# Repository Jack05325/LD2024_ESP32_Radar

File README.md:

# LD2420 Radar ESP32

## Descrizione del Progetto

Questo progetto contiene i file di progettazione PCB per un modulo radar basato sul sensore LD2420 integrato con un microcontrollore ESP32. Il sensore LD2420 è un radar a onde millimetriche a 24GHz per il rilevamento di presenza umana, ideale per applicazioni di domotica e automazione.

### Caratteristiche Principali

- **Sensore Radar**: LD2420 a 24GHz per rilevamento preciso di presenza e movimento
- **Microcontrollore**: ESP32 con connettività WiFi e Bluetooth integrata
- **Formato PCB**: Design compatto e ottimizzato per facile integrazione
- **Output**: Dati di rilevamento elaborabili via WiFi/Bluetooth

### Contenuto del Repository

- **File KiCad**: Schema elettrico (.kicad_sch) e layout PCB (.kicad_pcb)
- **BOM**: Bill of Materials nella cartella `/bom`
- **Gerber**: File pronti per la produzione nella cartella `/gerber_to_order`
- **PDF**: Schema elettrico esportato in formato PDF
- **Backup**: Versioni precedenti del progetto in `/LD2420_Radar_ESP32-backups`

### Software Richiesto

- KiCad 7.0 o superiore per aprire e modificare i file di progetto

### Note di Produzione

I file Gerber pronti per l'ordine sono disponibili nella cartella `gerber_to_order`. Consultare il PDF dello schema per i dettagli sul circuito.

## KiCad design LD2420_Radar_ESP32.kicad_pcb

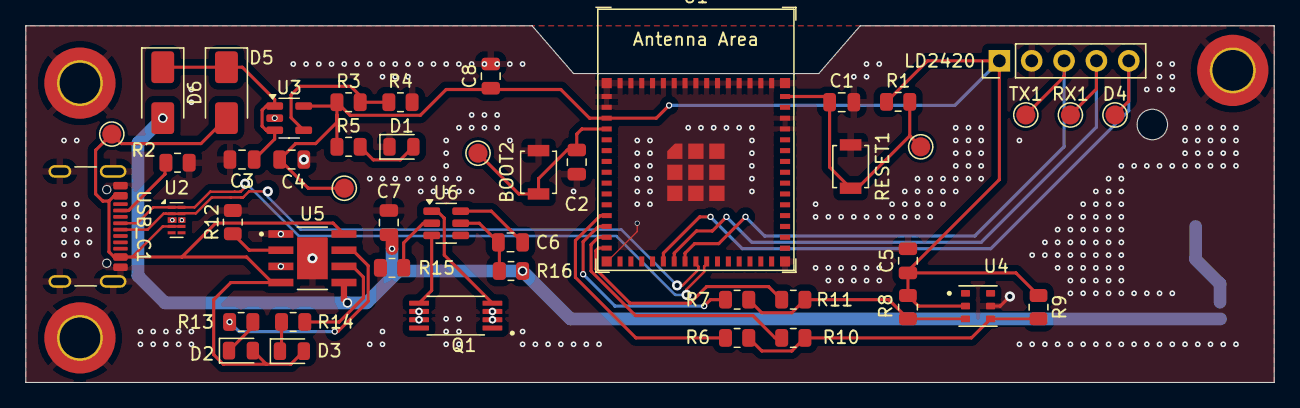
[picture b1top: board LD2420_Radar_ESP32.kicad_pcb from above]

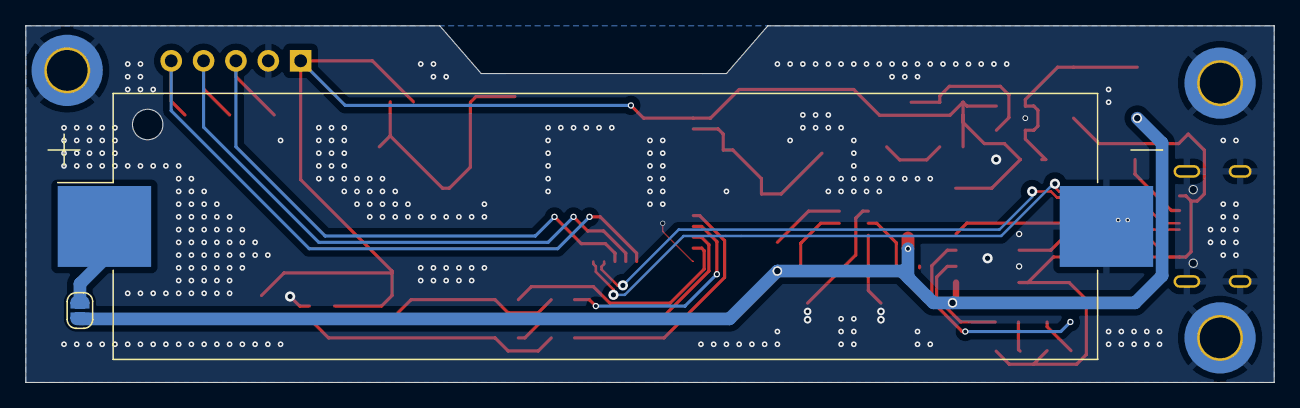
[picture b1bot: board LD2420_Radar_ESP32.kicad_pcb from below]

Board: 2 copper layers, 98.0 x 28.0 mm, 52 parts (2 on the bottom side), 32 nets.

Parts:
3.3V1: TestPoint; TestPoint_Pad_D1.5mm
BOOT1: TestPoint; TestPoint_Pad_D1.5mm
BOOT2: SW_Push; SW_SPST_B3U-1000P
BT1: Battery_Cell; BatteryHolder_Keystone_1042_1x18650
C1, C2, C5: 0.1uF; C_0805_2012Metric
C3, C4, C7, C8: 10uF; C_0805_2012Metric
C6: 100nF; C_0805_2012Metric
D1, D2, D3: LED; LED_0805_2012Metric
D4: TestPoint; TestPoint_Pad_D1.5mm
D5, D6: D; D_SMA
H1, H2, H3: MountingHole_Pad; MountingHole_3.2mm_M3_DIN965_Pad_TopBottom
JP1: Jumper_2_Open; SolderJumper-2_P1.3mm_Open_RoundedPad1.0x1.5mm
LD2420: Conn_01x05_Pin; PinHeader_1x05_P2.54mm_Vertical
Q1: FS8205A; SOP65P640X120-8N
R1: 10K; R_0805_2012Metric
R2: 5.1K; R_0805_2012Metric
R3: 1M; R_0805_2012Metric
R4: 200K; R_0805_2012Metric
R5: 5.1k; R_0805_2012Metric
R6, R7, R10, R11: 0; R_0805_2012Metric
R8, R9: 4.7k; R_0805_2012Metric
R12: 1.2K; R_0805_2012Metric
R13, R14: 1K; R_0805_2012Metric
R15: 1k; R_0805_2012Metric
R16: 100; R_0805_2012Metric
RESET1: SW_Push; SW_SPST_B3U-1000P
RESET2: TestPoint; TestPoint_Pad_D1.5mm
RX1: TestPoint; TestPoint_Pad_D1.5mm
TX1: TestPoint; TestPoint_Pad_D1.5mm
U1: ESP32-S3-MINI-1
U2: D3V3XA4B10LP; Diodes_UDFN-10_1.0x2.5mm_P0.5mm
U3: TLV75801PDBV; SOT-23-5
U4: AHT20; PSON100P300X300X110-6N
U5: TP4056-42-ESOP8; SOIC127P600X175-9N
U6: DW01A; SOT-23-6
USB_C1: USB_C_Plug_USB2.0; USB_C_Receptacle_GCT_USB4105-xx-A_16P_TopMnt_Horizontal
VBUS1: TestPoint; TestPoint_Pad_D1.5mm

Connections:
+3.3V: 3.3V1.1, C4.1, C5.1, C8.1, LD2420.1, R1.1, R3.1, R5.1, R8.1, R9.1, U1.3 (3V3), U3.5 (OUT), U4.2 (VDD)
CHRG_LED: R13.2, U5.7 (~CHRG)
GND: BOOT2.2, BT1.2 (-), C1.2, C2.2, C3.2, C4.2, C5.2, C7.1, C8.2, D1.1 (K), H1.1, H2.1, H3.1, LD2420.2, Q1.2, Q1.3, Q1.6, Q1.7, R2.2, R4.2, R12.2, R15.2, RESET1.1, U1.1 (GND), U1.2 (GND), U1.42 (GND), U1.43 (GND), U1.46 (GND), U1.47 (GND), U1.48 (GND), U1.49 (GND), U1.50 (GND), U1.51 (GND), U1.52 (GND), U1.53 (GND), U1.54 (GND), U1.55 (GND), U1.56 (GND), U1.57 (GND), U1.58 (GND), U1.59 (GND), U1.60 (GND), U1.61 (GND), U1.62 (GND), U1.63 (GND), U1.64 (GND), U1.65 (GND), U2.3 (VSS), U2.8 (VSS), U3.2 (GND), U4.5 (GND), U5.1 (TEMP), U5.3 (GND), U5.9 (EXP), USB_C1.A1 (GND), USB_C1.A12 (GND), USB_C1.B1 (GND), USB_C1.B12 (GND), USB_C1.S1 (SHIELD)
LD2420_DETECTION_PIN: D4.1, LD2420.5, U1.20 (GPIO16/U0CTS/ADC2_CH5/XTAL_32K_N)
LD2420_RX: LD2420.4, RX1.1, U1.21 (GPIO17/U1TXD/ADC2_CH6)
LD2420_TX: LD2420.3, TX1.1, U1.22 (GPIO18/U1RXD/ADC2_CH7/CLK_OUT3)
unnamed: BT1.1 (+), JP1.2 (B)
unnamed: D1.2 (A), R5.2
unnamed: D2.1 (K), R13.1
unnamed: D3.1 (K), R14.2
unnamed: C3.1, D5.1 (K), D6.1 (K), U3.1 (IN), U3.3 (EN)
unnamed: C1.1, R1.2, RESET1.2, RESET2.1, U1.45 (EN)
unnamed: BOOT1.1, BOOT2.1, C2.1, U1.4 (GPIO0/BOOT)
unnamed: R6.1, U1.12 (GPIO8/TOUCH8/ADC1_CH7/SUBSPICS1)
unnamed: R7.1, U1.13 (GPIO9/TOUCH9/ADC1_CH8/FSPIHD/SUBSPIHD)
unnamed: R10.1, U1.14 (GPIO10/TOUCH10/ADC1_CH9/FSPICS0/FSPIIO4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)
unnamed: R11.1, U1.15 (GPIO11/TOUCH11/ADC2_CH0/FSPID/FSPIIO5/S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)
unnamed: R3.2, R4.1, U3.4 (FB)
unnamed: R12.1, U5.2 (PROG)
unnamed: R15.1, U6.2 (CS)
unnamed: C6.2, U6.6 (GND)
unnamed: Q1.5, U6.3 (OC)
unnamed: Q1.4, U6.1 (OD)
unnamed: C6.1, R16.2, U6.5 (VCC)
unnamed: R2.1, USB_C1.A5 (CC)
SCL: R7.2, R8.2, R11.2, U4.3 (SCL)
SDA: R6.2, R9.2, R10.2, U4.4 (SDA)
STDBY_LED: R14.1, U5.6 (~STDBY)
USB_D+: U1.24 (GPIO20/U1CTS/ADC2_CH9/CLK_OUT1/USB_D+), U2.1, U2.10 (NC), USB_C1.A6 (D+)
USB_D-: U1.23 (GPIO19/U1RTS/ADC2_CH8/CLK_OUT2/USB_D-), U2.2, U2.9 (NC), USB_C1.A7 (D-)
VBATT: C7.2, D6.2 (A), JP1.1 (A), R16.1, U5.5 (BAT)
VBUS: D2.2 (A), D3.2 (A), D5.2 (A), U2.4, U2.7 (NC), U5.4 (VCC), U5.8 (CE), USB_C1.A4 (VBUS), USB_C1.A9 (VBUS), USB_C1.B4 (VBUS), USB_C1.B9 (VBUS), VBUS1.1

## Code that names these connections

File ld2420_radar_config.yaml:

esphome:
  name: ld2420_radar
  platformio_options:
    build_flags: 
      -DARDUINO_USB_CDC_ON_BOOT=1
      -DARDUINO_USB_MODE=1
  on_boot:
    priority: -100
    then:
      - logger.log: "Boot completato in modalità sicura"

esp32:
  board: esp32-s3-devkitc-1
  variant: esp32s3
  framework:
    type: arduino

wifi:
  ssid: !secret ssid
  password: !secret wifi_psw

ota:
  - platform: esphome
    password: !secret ota_psw

api:
  encryption:
    key: "tD4JJkO0P1YAfMLdvpjBFxyPb4QR+PrrIR6dX85RqXE="

web_server:
  port: 80
  auth:
    username: admin
    password: "admin"

logger:
  baud_rate: 115200

deep_sleep:
  id: deep_sleep_1
  run_duration: 10s         # tempo in cui resta sveglio per leggere/sincronizzare
  sleep_duration: 30s       # si ri-sveglia comunque ogni 30 secondi
  wakeup_pin:
    number: GPIO16          # pin esterno che può risvegliare anche prima del timer
  wakeup_pin_mode: INVERT_WAKEUP


uart:
  id: ld2420_uart
  tx_pin: GPIO17   # ESP32 → LD2420_RX
  rx_pin: GPIO18   # ESP32 ← LD2420_TX
  baud_rate: 115200
  parity: NONE
  stop_bits: 1

ld2420:
  uart_id: ld2420_uart

i2c:
  sda: 10
  scl: 11
  scan: true
  id: bus_a

text_sensor:
  - platform: ld2420
    fw_version:
      name: Versione firmware

sensor:
  - platform: ld2420
    moving_distance:
      name: Distanza di movimento
  
  - platform: aht10
    variant: AHT20
    i2c_id: bus_a
    temperature:
      name: "Temperature"
    humidity:
      name: "Humidity"
    update_interval: 10s

binary_sensor:
  - platform: ld2420
    has_target:
      name: Presenza

  #- platform: gpio
  #  pin:
  #    number: GPIO16
  #    mode: INPUT_PULLUP
  #  name: "Stato GPIO16"
  #  id: "deep_sleep_pin"
  #  device_class: opening

switch:
  - platform: restart
    name: Riavvio nodo ESPHome

select:
  - platform: ld2420
    operating_mode:
      name: Modalità operativa

number:
  - platform: ld2420
    presence_timeout:
      name: Timeout di rilevazione presenza
    min_gate_distance:
      name: Distanza minima gate
    max_gate_distance:
      name: Distanza massima gate
    gate_select:
      name: Selezione gate
    still_threshold:
      name: Impostazione soglia immobilità
    move_threshold:
      name: Impostazione soglia movimento

button:
  - platform: ld2420
    apply_config:
      name: Applica configurazione
    factory_reset:
      name: Reset a impostazioni di fabbrica
    restart_module:
      name: Riavvio modulo
    revert_config:
      name: Undo modifiche

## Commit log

2026-02-16 Inizializzazione dei file del progetto
2026-02-16 Configurazione per ESPHome
